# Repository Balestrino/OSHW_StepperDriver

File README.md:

OSHW_StepperDriver
==================

Version 0.6.2 beta

License: CC BY-SA

Software: Eagle CAD v6.4

Stepper motor driver (A4989 and IRLR024)

Description:
Powerful stepper motor driver up to 15A peak.

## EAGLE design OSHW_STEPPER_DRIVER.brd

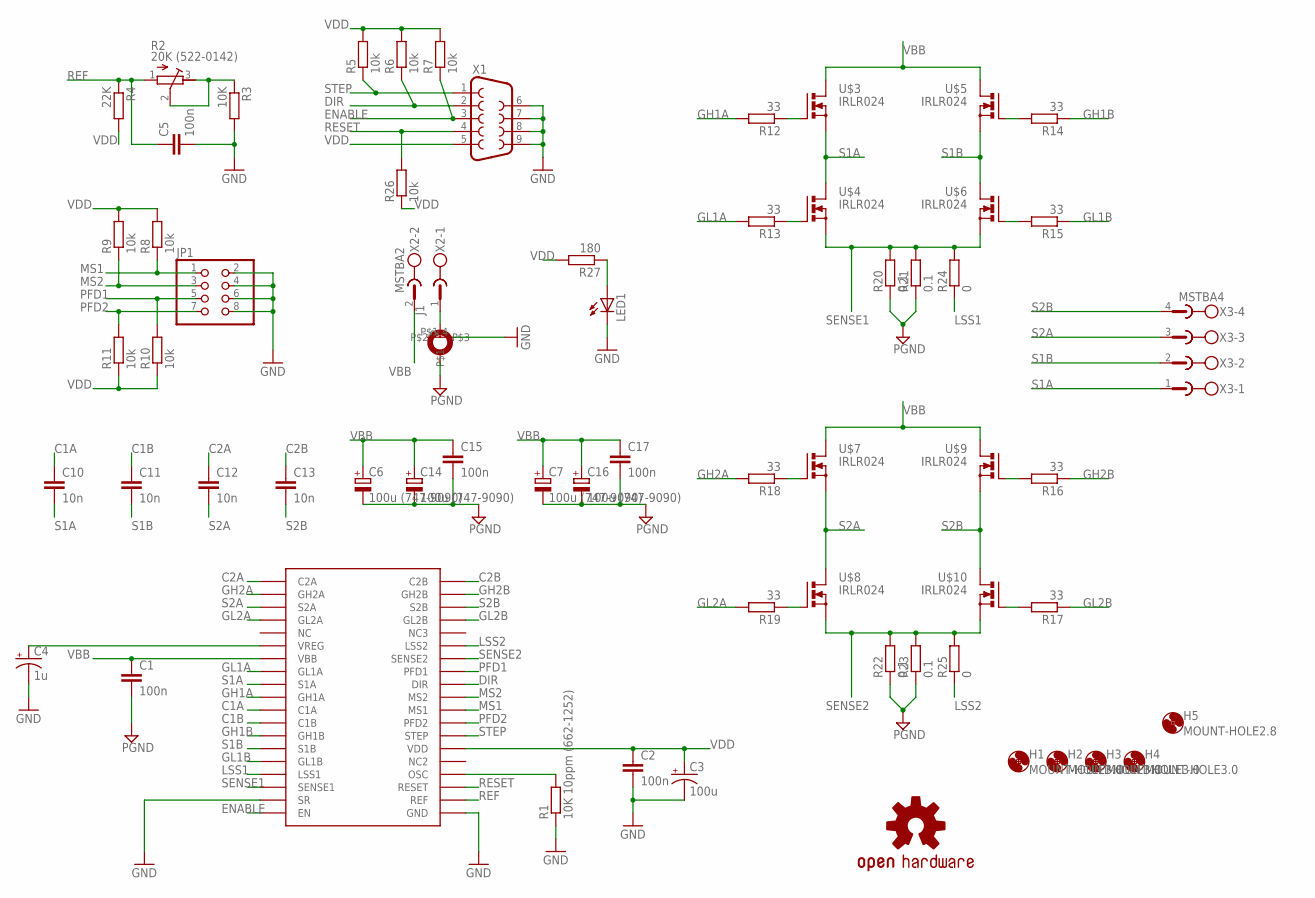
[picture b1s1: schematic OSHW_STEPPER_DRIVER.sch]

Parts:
C1, C2, C5: 100n; C0805
C3: 100u; 153CLV-0605
C4: 1u; 153CLV-0405
C6, C7, C14, C16: 100u (747-9090); PANASONIC_G
C10, C11, C12, C13: 10n; C0805
C15, C17: 100n; C1210
H1, H2, H3, H4: MOUNT-HOLE3.0; 3,0
H5: MOUNT-HOLE2.8; 2,8
J1: STARBOARD_GND; STARBOARD_GROUND
JP1: PINHD-2X4; 2X04
LED1: LEDSIDELED; OSRAM-SIDELED
R1: 10K 10ppm (662-1252); R0805
R2: 20K (522-0142); RTRIM3296P
R3: 10K; R0603
R4: 22K; R0603
R5, R6, R7, R8, R9, R10, R11, R26: 10k; R0603
R12, R13, R14, R15, R16, R17, R18, R19: 33; R0603
R20, R21, R22, R23: 0.1; R2512
R24, R25: 0; R0805
R27: 180; R0603
U$1: OSHW-LOGOM; OSHW-LOGO-M
U$2: A4989; TSSOP38
U$3, U$4, U$5, U$6, U$7, U$8, U$9, U$10: IRLR024; D-PAK_TO252AA
X1: DB9FEMALE; DB9
X2: MSTBA2
X3: MSTBA4

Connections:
C1A: C10.1, U$2.P$11 (C1A)
C1B: C11.1, U$2.P$12 (C1B)
C2A: C12.1, U$2.P$1 (C2A)
C2B: C13.1, U$2.P$38 (C2B)
DIR: R6.1, U$2.P$30 (DIR), X1.2
ENABLE: R7.1, U$2.P$19 (EN), X1.3
GH1A: R12.2, U$2.P$10 (GH1A)
GH1B: R14.1, U$2.P$13 (GH1B)
GH2A: R18.2, U$2.P$2 (GH2A)
GH2B: R16.1, U$2.P$37 (GH2B)
GL1A: R13.2, U$2.P$8 (GL1A)
GL1B: R15.1, U$2.P$15 (GL1B)
GL2A: R19.2, U$2.P$4 (GL2A)
GL2B: R17.1, U$2.P$35 (GL2B)
GND: C2.2, C3.-, C4.-, C5.2, J1.1 (MOUNT), JP1.2, JP1.4, JP1.6, JP1.8, LED1.C, R1.1, R3.2, U$2.P$18 (SR), U$2.P$20 (GND), X1.6, X1.7, X1.8, X1.9
LSS1: R24.1, U$2.P$16 (LSS1)
LSS2: R25.1, U$2.P$33 (LSS2)
MS1: JP1.1, R8.1, U$2.P$28 (MS1)
MS2: JP1.3, R9.1, U$2.P$29 (MS2)
unnamed: C4.+, U$2.P$6 (VREG)
unnamed: R1.2, U$2.P$23 (OSC)
unnamed: R2.2 (S), R2.3 (A), R3.1
unnamed: J1.2, X2.1
unnamed: R12.1, U$3.G (GATE)
unnamed: R13.1, U$4.G (GATE)
unnamed: R14.2, U$5.G (GATE)
unnamed: R15.2, U$6.G (GATE)
unnamed: R16.2, U$9.G (GATE)
unnamed: R17.2, U$10.G (GATE)
unnamed: R18.1, U$7.G (GATE)
unnamed: R19.1, U$8.G (GATE)
unnamed: LED1.A, R27.1
PFD1: JP1.5, R10.2, U$2.P$31 (PFD1)
PFD2: JP1.7, R11.2, U$2.P$27 (PFD2)
PGND: C1.2, C6.-, C7.-, C14.-, C15.2, C16.-, C17.2, J1.4, R20.1, R21.1, R22.1, R23.1
REF: C5.1, R2.1 (E), R4.1, U$2.P$21 (REF)
RESET: R26.2, U$2.P$22 (RESET), X1.4
S1A: C10.2, U$2.P$9 (S1A), U$3.S (SOURCE), U$4.D (DRAIN), U$4.DRAIN-BOTTOM (DRAIN), X3.1
S1B: C11.2, U$2.P$14 (S1B), U$5.S (SOURCE), U$6.D (DRAIN), U$6.DRAIN-BOTTOM (DRAIN), X3.2
S2A: C12.2, U$2.P$3 (S2A), U$7.S (SOURCE), U$8.D (DRAIN), U$8.DRAIN-BOTTOM (DRAIN), X3.3
S2B: C13.2, U$2.P$36 (S2B), U$9.S (SOURCE), U$10.D (DRAIN), U$10.DRAIN-BOTTOM (DRAIN), X3.4
SENSE1: R20.2, R21.2, R24.2, U$2.P$17 (SENSE1), U$4.S (SOURCE), U$6.S (SOURCE)
SENSE2: R22.2, R23.2, R25.2, U$2.P$32 (SENSE2), U$8.S (SOURCE), U$10.S (SOURCE)
STEP: R5.1, U$2.P$26 (STEP), X1.1
VBB: C1.1, C6.+, C7.+, C14.+, C15.1, C16.+, C17.1, U$2.P$7 (VBB), U$3.D (DRAIN), U$3.DRAIN-BOTTOM (DRAIN), U$5.D (DRAIN), U$5.DRAIN-BOTTOM (DRAIN), U$7.D (DRAIN), U$7.DRAIN-BOTTOM (DRAIN), U$9.D (DRAIN), U$9.DRAIN-BOTTOM (DRAIN), X2.2
VDD: C2.1, C3.+, R4.2, R5.2, R6.2, R7.2, R8.2, R9.2, R10.1, R11.1, R26.1, R27.2, U$2.P$25 (VDD), X1.5

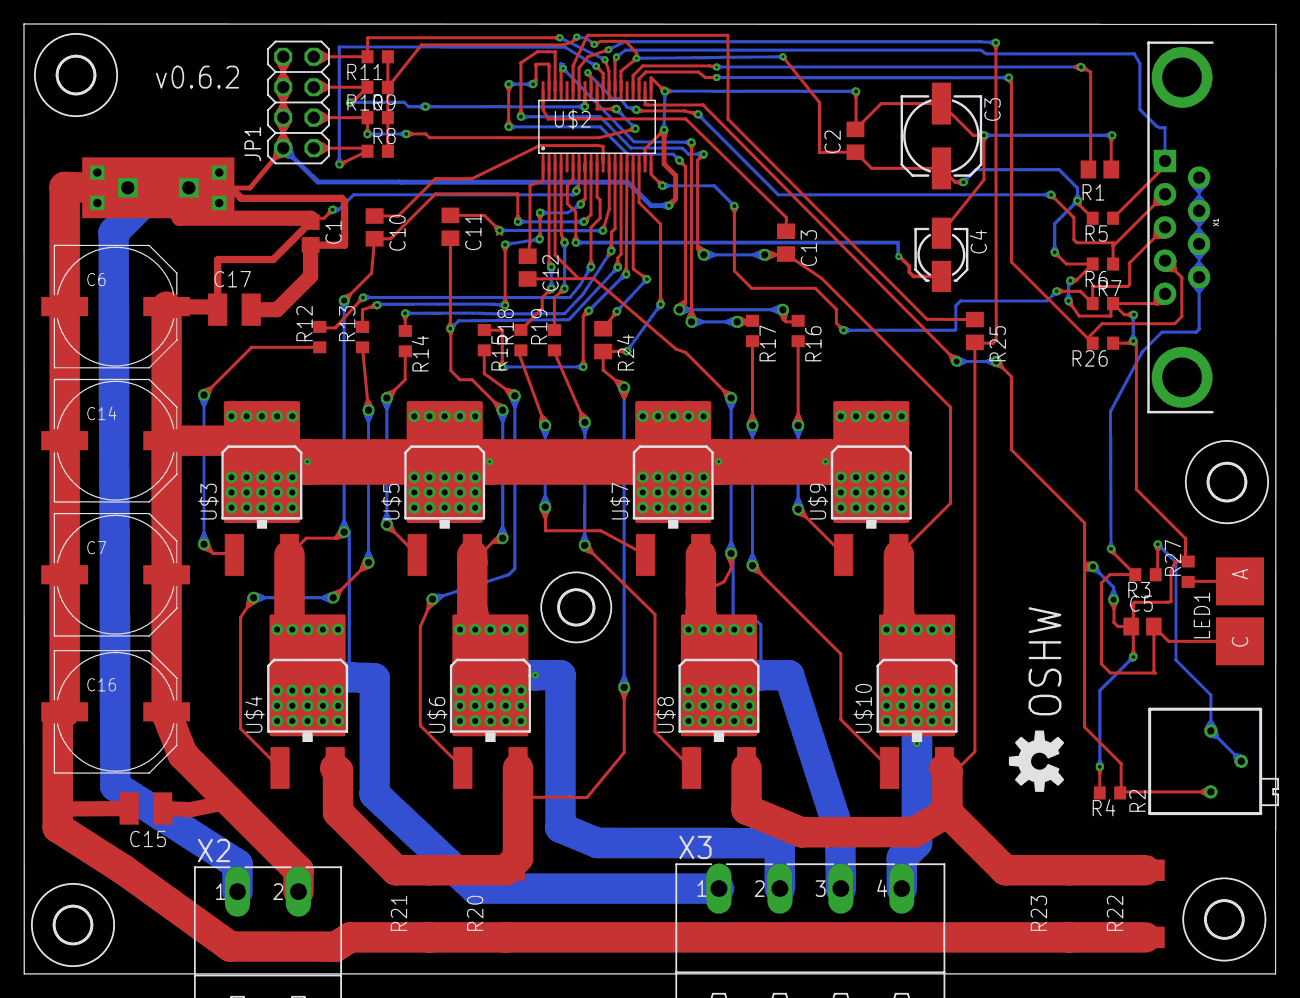
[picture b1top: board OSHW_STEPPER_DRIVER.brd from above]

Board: 2 copper layers, 104.4 x 79.2 mm, 63 parts (0 on the bottom side), 46 nets.

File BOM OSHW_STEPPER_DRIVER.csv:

"Qty";"Value";"Device";"Package";"Parts";"Description";"MF";"MPN";"OC_FARNELL";"OC_NEWARK";
"1";"";"DB9FEMALE";"DB9";"X1";"DB9 Connector";"";"";"";"";
"1";"";"LEDSIDELED";"OSRAM-SIDELED";"LED1";"LED";"";"";"";"";
"1";"";"PINHD-2X4";"2X04";"JP1";"PIN HEADER";"";"";"";"";
"1";"";"STARBOARD_GND";"STARBOARD_GROUND";"J1";"StarBoard ground Pad";"";"";"";"";
"2";"0";"R-EU_R0805";"R0805";"R24, R25";"RESISTOR, European symbol";"";"";"";"";
"4";"0.1";"R-EU_R2512";"R2512";"R20, R21, R22, R23";"RESISTOR, European symbol";"";"";"";"";
"3";"100n";"C-EUC0805";"C0805";"C1, C2, C5";"CAPACITOR, European symbol";"";"";"";"";
"2";"100n";"C-EUC1210";"C1210";"C15, C17";"CAPACITOR, European symbol";"";"";"";"";
"2";"100u";"CPOL-US153CLV-0605";"153CLV-0605";"C3, C4";"POLARIZED CAPACITOR, American symbol";"";"";"";"";
"4";"100u (747-9090)";"CPOL-EUG";"PANASONIC_G";"C6, C7, C14, C16";"POLARIZED CAPACITOR, European symbol";"";"";"";"";
"1";"10K";"R-EU_R0603";"R0603";"R3";"RESISTOR, European symbol";"";"";"";"";
"1";"10K 10ppm (662-1252)";"R-EU_R0805";"R0805";"R1";"RESISTOR, European symbol";"";"";"";"";
"8";"10k";"R-EU_R0603";"R0603";"R5, R6, R7, R8, R9, R10, R11, R26";"RESISTOR, European symbol";"";"";"";"";
"4";"10n";"C-EUC0805";"C0805";"C10, C11, C12, C13";"CAPACITOR, European symbol";"";"";"";"";
"1";"180";"R-EU_R0603";"R0603";"R27";"RESISTOR, European symbol";"";"";"";"";
"1";"20K (522-0142)";"R-TRIMM3296P";"RTRIM3296P";"R2";"Trimm resistor";"";"";"";"";
"1";"22K";"R-EU_R0603";"R0603";"R4";"RESISTOR, European symbol";"";"";"";"";
"8";"33";"R-EU_R0603";"R0603";"R12, R13, R14, R15, R16, R17, R18, R19";"RESISTOR, European symbol";"";"";"";"";
"1";"A4989";"A4989";"TSSOP38";"U$2";"";"";"";"";"";
"8";"IRLR024";"IRLR024";"D-PAK_TO252AA";"U$3, U$4, U$5, U$6, U$7, U$8, U$9, U$10";"";"";"";"";"";
"1";"MOUNT-HOLE2.8";"MOUNT-HOLE2.8";"2,8";"H5";"MOUNTING HOLE with drill center marker";"";"";"";"";
"4";"MOUNT-HOLE3.0";"MOUNT-HOLE3.0";"3,0";"H1, H2, H3, H4";"MOUNTING HOLE with drill center marker";"";"";"";"";
"1";"MSTBA2";"MSTBA2";"MSTBA2";"X2";"PHOENIX";"FARNELL";"1757242";"3705171";"71C4161";
"1";"MSTBA4";"MSTBA4";"MSTBA4";"X3";"PHOENIX";"FARNELL";"1757268";"3705195";"71C4163";
"1";"OSHW-LOGOM";"OSHW-LOGOM";"OSHW-LOGO-M";"U$1";"Open Source Hardware Logo This logo indicates the piece of hardware it is found on incorporates a OSHW license and/or adheres to the definition of open source hardware found here: http://freedomdefined.org/OSHW";"";"";"";"";

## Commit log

2013-06-16 schematic
2013-06-23 modified: OSHW_STEPPER_DRIVER.sch
2013-06-23 pcb board file: OSHW_STEPPER_DRIVER.brd screenshot of schematic
2013-06-23 V0.6
2013-06-23 PCB screenshot
2013-06-23 rework of some GND signals, added version text on PCB
2013-06-24 added BOM
2013-08-23 minor fix, added teardrops
2013-08-23 REF fix
2013-08-23 0.6.2 beta
2013-12-20 updated Creg footprint and value

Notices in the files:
parts and their libraries:
SparkFun: Licensing: CC v3.0 Share-Alike You are welcome to use this library for commercial purposes.
